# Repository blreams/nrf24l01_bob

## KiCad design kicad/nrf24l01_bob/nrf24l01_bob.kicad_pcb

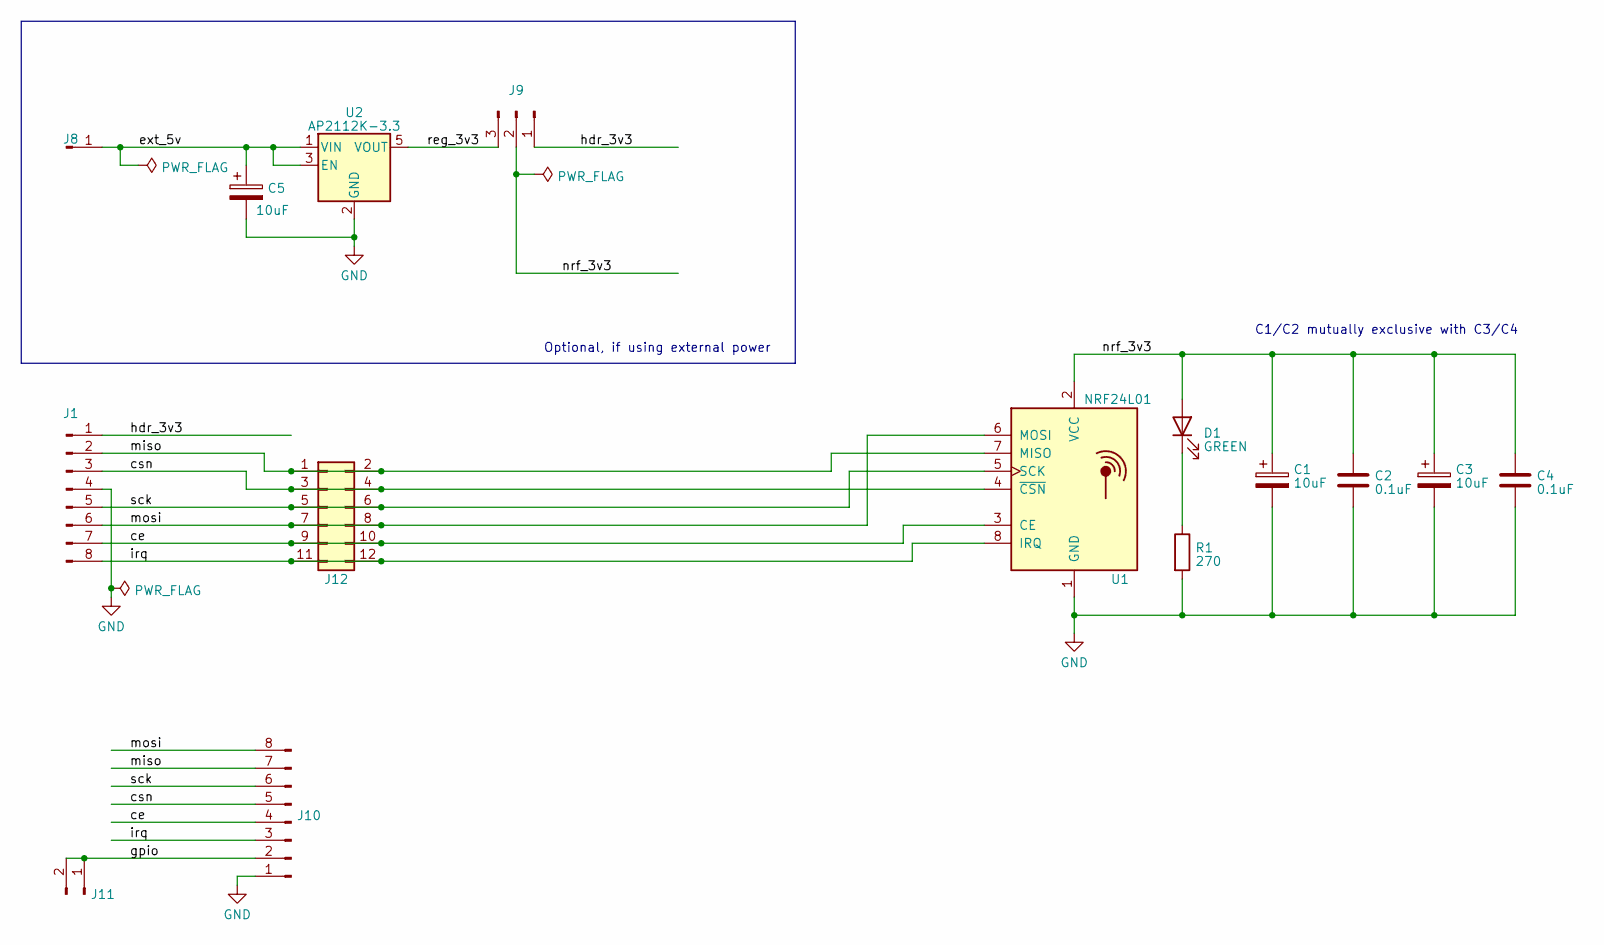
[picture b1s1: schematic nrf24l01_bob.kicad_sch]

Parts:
C1, C5: 10uF; CP_Radial_D5.0mm_P2.50mm
C2: 0.1uF; C_Disc_D4.7mm_W2.5mm_P5.00mm
C3: 10uF; CP_Elec_5x3.9
C4: 0.1uF; C_0805_2012Metric_Pad1.18x1.45mm_HandSolder
D1: GREEN; LED_D3.0mm
J1, J10: Conn_01x08_Pin; PinHeader_1x08_P2.54mm_Vertical
J8: Conn_01x01_Pin; PinHeader_1x01_P2.54mm_Vertical
J9: Conn_01x03_Pin; PinHeader_1x03_P2.54mm_Vertical
J11: Conn_01x02_Pin; PinHeader_1x02_P2.54mm_Vertical
J12: Conn_02x06_Odd_Even; PinHeader_2x06_P2.54mm_Vertical
R1: 270; R_Axial_DIN0207_L6.3mm_D2.5mm_P10.16mm_Horizontal
U1: NRF24L01; nRF24L01_Breakout
U2: AP2112K-3.3; SOT-23-5

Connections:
/ce: J1.7, J10.4, J12.9, J12.10, U1.3 (CE)
/csn: J1.3, J10.5, J12.3, J12.4, U1.4 (~CSN)
/ext_5v: C5.1, J8.1, U2.1 (VIN), U2.3 (EN)
/gpio: J10.2, J11.1, J11.2
/hdr_3v3: J1.1, J9.1
/irq: J1.8, J10.3, J12.11, J12.12, U1.8 (IRQ)
/miso: J1.2, J10.7, J12.1, J12.2, U1.7 (MISO)
/mosi: J1.6, J10.8, J12.7, J12.8, U1.6 (MOSI)
/nrf_3v3: C1.1, C2.1, C3.1, C4.1, D1.2 (A), J9.2, U1.2 (VCC)
/reg_3v3: J9.3, U2.5 (VOUT)
/sck: J1.5, J10.6, J12.5, J12.6, U1.5 (SCK)
GND: C1.2, C2.2, C3.2, C4.2, C5.2, J1.4, J10.1, R1.2, U1.1 (GND), U2.2 (GND)
unnamed: D1.1 (K), R1.1

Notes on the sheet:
Optional, if using external power
C1/C2 mutually exclusive with C3/C4

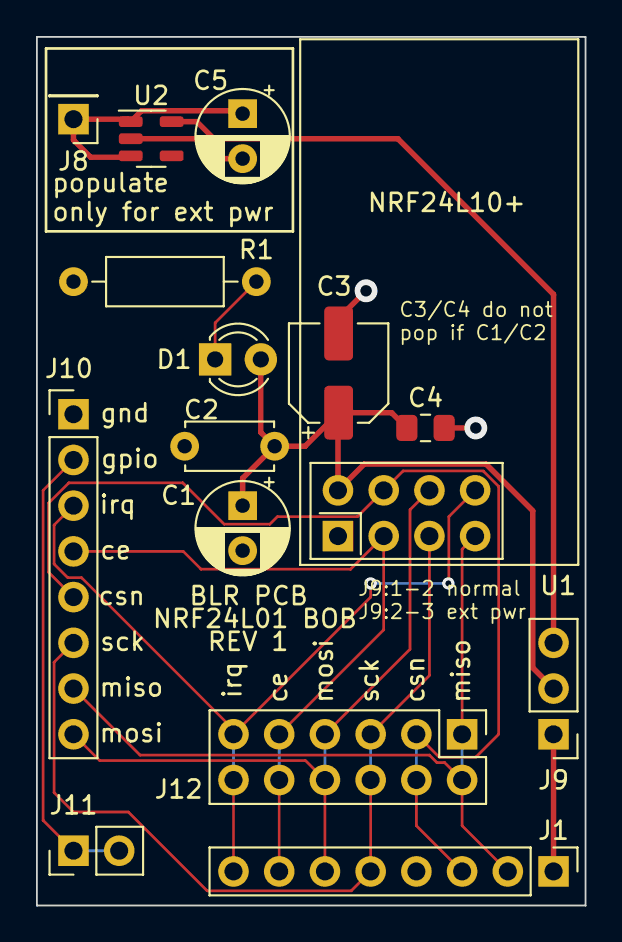
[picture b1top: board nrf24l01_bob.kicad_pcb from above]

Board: 2 copper layers, 30.5 x 48.3 mm, 15 parts (0 on the bottom side), 13 nets.
